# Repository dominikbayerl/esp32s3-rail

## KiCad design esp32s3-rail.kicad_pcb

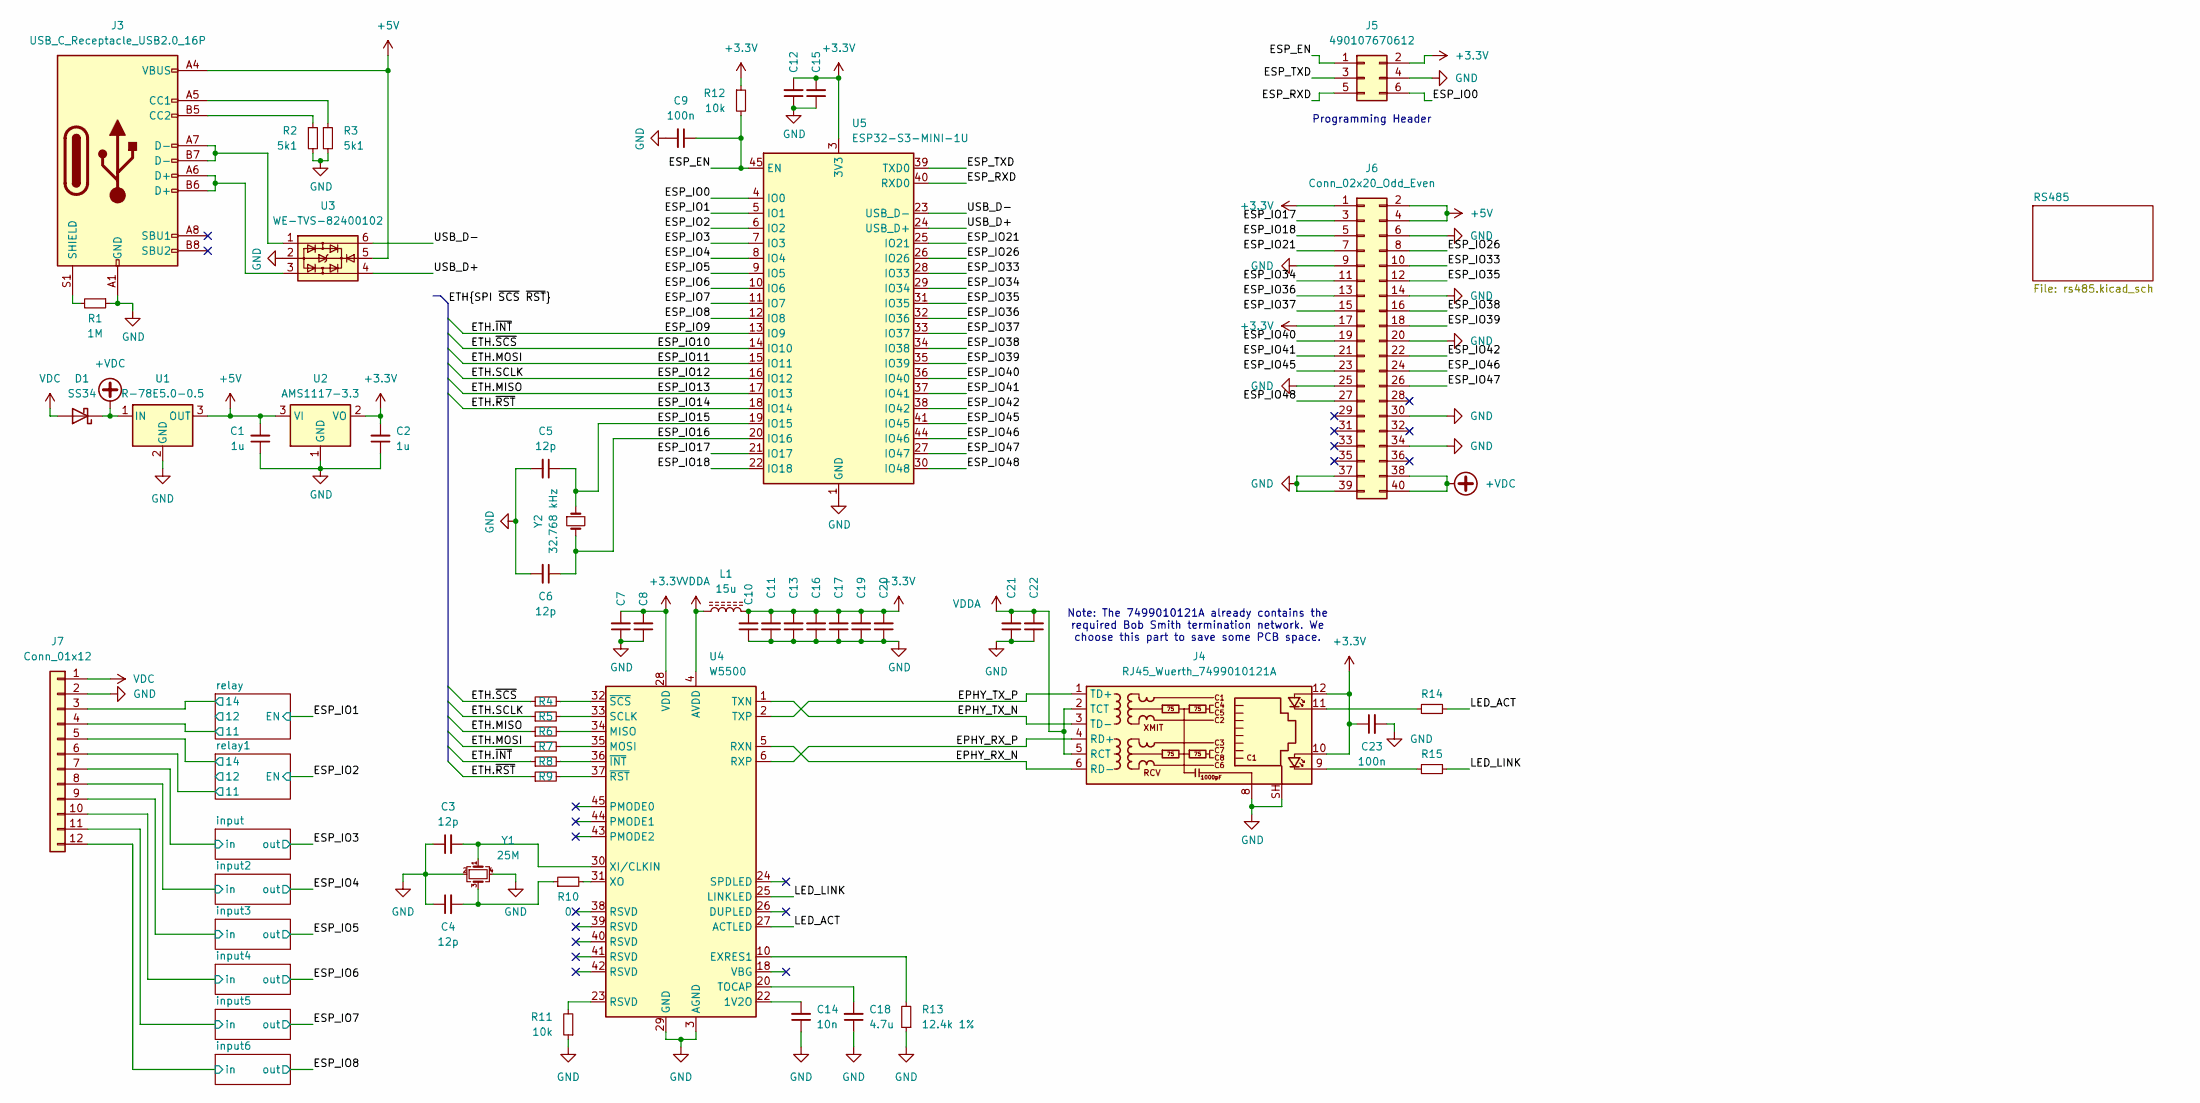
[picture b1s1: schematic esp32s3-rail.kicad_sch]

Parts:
C1, C2, C7, C8, C10, C11, C12, C13, C15, C16, C19, C20: 1u; C_0603_1608Metric_Pad1.08x0.95mm_HandSolder
C3, C4, C5, C6: 12p; C_0603_1608Metric_Pad1.08x0.95mm_HandSolder
C9, C21, C23: 100n; C_0603_1608Metric_Pad1.08x0.95mm_HandSolder
C14: 10n; C_0603_1608Metric_Pad1.08x0.95mm_HandSolder
C17: 10u; C_0603_1608Metric_Pad1.08x0.95mm_HandSolder
C18: 4.7u; C_0603_1608Metric_Pad1.08x0.95mm_HandSolder
C22: 1n; C_0603_1608Metric_Pad1.08x0.95mm_HandSolder
D1: SS34; D_SOD-123
J3: USB_C_Receptacle_USB2.0_16P; USB_C_Receptacle_HRO_TYPE-C-31-M-12
J4: RJ45_Wuerth_7499010121A; RJ45_Wuerth_7499010121A_Horizontal
J5: 490107670612; Würth_WR-WST_debug_490107670612_2x03_P2.54mm_Vertical
J6: Conn_02x20_Odd_Even; PinSocket_2x20_P2.54mm_Vertical
J7: Conn_01x12; Molex_SPOX_5268-12A_1x12_P2.50mm_Horizontal
L1: 15u; L_0603_1608Metric_Pad1.05x0.95mm_HandSolder
R1: 1M; R_0603_1608Metric_Pad0.98x0.95mm_HandSolder
R2, R3: 5k1; R_0603_1608Metric_Pad0.98x0.95mm_HandSolder
R4, R5, R6, R7, R8, R9: 20; R_0603_1608Metric_Pad0.98x0.95mm_HandSolder
R10: 0; R_0603_1608Metric_Pad0.98x0.95mm_HandSolder
R11, R12: 10k; R_0603_1608Metric_Pad0.98x0.95mm_HandSolder
R13: 12.4k 1%; R_0603_1608Metric_Pad0.98x0.95mm_HandSolder
R14, R15: 1k; R_0603_1608Metric_Pad0.98x0.95mm_HandSolder
U1: R-78E5.0-0.5; Converter_DCDC_RECOM_R-78E-0.5_THT
U2: AMS1117-3.3; SOT-223-3_TabPin2
U3: WE-TVS-82400102; SOT-23-6
U4: W5500; LQFP-48_7x7mm_P0.5mm
U5: ESP32-S3-MINI-1U; ESP32-S2-MINI-1U
Y1: 25M; Crystal_SMD_3225-4Pin_3.2x2.5mm_HandSoldering
Y2: 32.768 kHz; Crystal_SMD_3215-2Pin_3.2x1.5mm

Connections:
+3.3V: C2.2, C7.2, C8.2, C10.2, C11.2, C12.2, C13.2, C15.2, C16.2, C17.2, C19.2, C20.2, C23.1, J4.10, J4.12, J5.2, J6.1, J6.17, L1.2, R12.1, U2.2 (VO), U4.28 (VDD), U5.3 (3V3); also elsewhere on the board
+5V: C1.2, J3.A4 (VBUS), J3.A9 (VBUS), J3.B4 (VBUS), J3.B9 (VBUS), J6.2, J6.4, U1.3 (OUT), U2.3 (VI), U3.5; also elsewhere on the board
+VDC: D1.1 (K), J6.38, J6.40, U1.1 (IN)
/EPHY_RX_N: J4.6 (RD-), U4.5 (RXN)
/EPHY_RX_P: J4.4 (RD+), U4.6 (RXP)
/EPHY_TX_N: J4.3 (TD-), U4.1 (TXN)
/EPHY_TX_P: J4.1 (TD+), U4.2 (TXP)
/ESP_EN: C9.1, J5.1, R12.2, U5.45 (EN)
/ESP_IO0: J5.6, U5.4 (IO0)
/ESP_IO1: U5.5 (IO1); also elsewhere on the board
/ESP_IO2: U5.6 (IO2); also elsewhere on the board
/ESP_IO3: U5.7 (IO3); also elsewhere on the board
/ESP_IO4: U5.8 (IO4); also elsewhere on the board
/ESP_IO5: U5.9 (IO5); also elsewhere on the board
/ESP_IO6: U5.10 (IO6); also elsewhere on the board
/ESP_IO7: U5.11 (IO7); also elsewhere on the board
/ESP_IO8: U5.12 (IO8); also elsewhere on the board
/ESP_IO15: C5.1, U5.19 (IO15), Y2.1
/ESP_IO16: C6.1, U5.20 (IO16), Y2.2
/ESP_IO17: J6.3, U5.21 (IO17)
/ESP_IO18: J6.5, U5.22 (IO18)
/ESP_IO21: J6.7, U5.25 (IO21)
/ESP_IO26: J6.8, U5.26 (IO26)
/ESP_IO33: J6.10, U5.28 (IO33)
/ESP_IO34: J6.11, U5.29 (IO34)
/ESP_IO35: J6.12, U5.31 (IO35)
/ESP_IO36: J6.13, U5.32 (IO36)
/ESP_IO37: J6.15, U5.33 (IO37)
/ESP_IO38: J6.16, U5.34 (IO38)
/ESP_IO39: J6.18, U5.35 (IO39)
/ESP_IO40: J6.19, U5.36 (IO40)
/ESP_IO41: J6.21, U5.37 (IO41)
/ESP_IO42: J6.22, U5.38 (IO42)
/ESP_IO45: J6.23, U5.41 (IO45)
/ESP_IO46: J6.24, U5.44 (IO46)
/ESP_IO47: J6.26, U5.27 (IO47)
/ESP_IO48: J6.27, U5.30 (IO48)
/ESP_RXD: J5.5, U5.40 (RXD0)
/ESP_TXD: J5.3, U5.39 (TXD0)
/ETH.MISO: R6.1, U5.17 (IO13)
/ETH.MOSI: R7.1, U5.15 (IO11)
/ETH.SCLK: R5.1, U5.16 (IO12)
/ETH.~INT: R8.1, U5.13 (IO9)
/ETH.~RST: R9.1, U5.18 (IO14)
/ETH.~SCS: R4.1, U5.14 (IO10)
/LED_ACT: R14.2, U4.27 (ACTLED)
/LED_LINK: R15.2, U4.25 (LINKLED)
/USB_D+: U3.4, U5.24 (USB_D+)
/USB_D-: U3.6, U5.23 (USB_D-)
/input2/in: J7.8; also elsewhere on the board
/input3/in: J7.9; also elsewhere on the board
/input4/in: J7.10; also elsewhere on the board
/input5/in: J7.11; also elsewhere on the board
/input6/in: J7.12; also elsewhere on the board
/input/in: J7.7; also elsewhere on the board
/relay1/11: J7.6; also elsewhere on the board
/relay1/14: J7.5; also elsewhere on the board
/relay/11: J7.4; also elsewhere on the board
/relay/14: J7.3; also elsewhere on the board
GND: C1.1, C2.1, C3.1, C4.1, C5.2, C6.2, C7.1, C8.1, C9.2, C10.1, C11.1, C12.1, C13.1, C14.1, C15.1, C16.1, C17.1, C18.1, C19.1, C20.1, C21.1, C22.1, C23.2, J3.A1 (GND), J3.A12 (GND), J3.B1 (GND), J3.B12 (GND), J4.8, J4.SH, J5.4, J6.6, J6.9, J6.14, J6.20, J6.25, J6.30, J6.34, J6.37, J6.39, J7.2, R1.1, R2.2, R3.2, R11.1, R13.1, U1.2 (GND), U2.1 (GND), U3.2, U4.3 (AGND), U4.9 (AGND), U4.14 (AGND), U4.16 (AGND), U4.19 (AGND), U4.29 (GND), U4.48 (AGND), U5.1 (GND), U5.2 (GND), U5.42 (GND), U5.43 (GND), U5.46 (GND), U5.47 (GND), U5.48 (GND), U5.49 (GND), U5.50 (GND), U5.51 (GND), U5.52 (GND), U5.53 (GND), U5.54 (GND), U5.55 (GND), U5.56 (GND), U5.57 (GND), U5.58 (GND), U5.59 (GND), U5.60 (GND), U5.61 (GND), U5.62 (GND), U5.63 (GND), U5.64 (GND), U5.65 (GND), Y1.2, Y1.4; also elsewhere on the board
unnamed: C4.2, R10.1, Y1.3
unnamed: J3.A5 (CC1), R3.1
unnamed: J3.B5 (CC2), R2.1
unnamed: J3.A6 (D+), J3.B6 (D+), U3.3
unnamed: J3.A7 (D-), J3.B7 (D-), U3.1
unnamed: J3.S1 (SHIELD), R1.2
unnamed: J4.9, R15.1
unnamed: J4.11, R14.1
unnamed: R11.2, U4.23 (RSVD)
unnamed: C14.2, U4.22 (1V2O)
unnamed: R13.2, U4.10 (EXRES1)
unnamed: R6.2, U4.34 (MISO)
unnamed: R7.2, U4.35 (MOSI)
unnamed: R5.2, U4.33 (SCLK)
unnamed: C18.2, U4.20 (TOCAP)
unnamed: C3.2, U4.30 (XI/CLKIN), Y1.1
unnamed: R10.2, U4.31 (XO)
unnamed: R8.2, U4.36 (~INT)
unnamed: R9.2, U4.37 (~RST)
unnamed: R4.2, U4.32 (~SCS)
VDC: D1.2 (A), J7.1
VDDA: C21.2, C22.2, J4.2 (TCT), J4.5 (RCT), L1.1, U4.4 (AVDD), U4.8 (AVDD), U4.11 (AVDD), U4.15 (AVDD), U4.17 (AVDD), U4.21 (AVDD)

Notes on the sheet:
Programming Header
Note: The 7499010121A already contains the required Bob Smith termination network. We choose this part to save some PCB space.

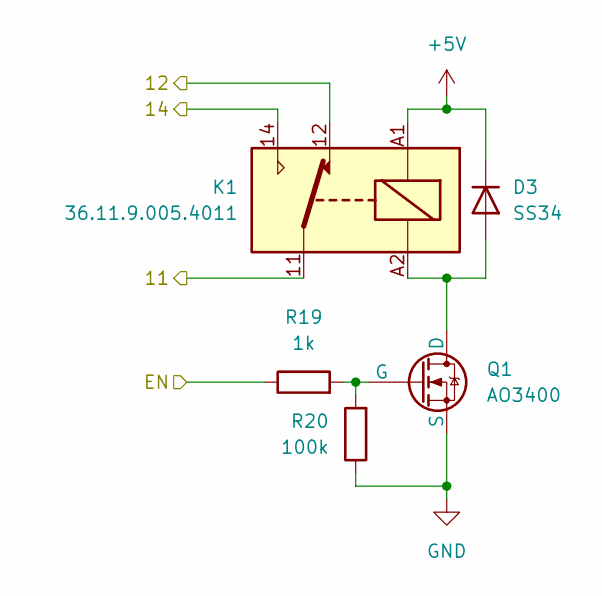
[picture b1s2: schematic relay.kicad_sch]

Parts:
D3: SS34; D_SOD-123
K1: 36.11.9.005.4011; Relay_SPDT_Finder_36.11
Q1: AO3400; SOT-23_Handsoldering
R19: 1k; R_0603_1608Metric_Pad0.98x0.95mm_HandSolder
R20: 100k; R_0603_1608Metric_Pad0.98x0.95mm_HandSolder

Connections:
+5V: D3.1 (K), K1.A1; also elsewhere on the board
/ESP_IO2: R19.1; also elsewhere on the board
/relay1/11: K1.11; also elsewhere on the board
/relay1/12: K1.12
/relay1/14: K1.14; also elsewhere on the board
GND: Q1.3 (S), R20.1; also elsewhere on the board
unnamed: D3.2 (A), K1.A2, Q1.1 (D)
unnamed: Q1.2 (G), R19.2, R20.2

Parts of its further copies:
D6: SS34; D_SOD-123
K2: 36.11.9.005.4011; Relay_SPDT_Finder_36.11
Q2: AO3400; SOT-23_Handsoldering
R27: 1k; R_0603_1608Metric_Pad0.98x0.95mm_HandSolder
R28: 100k; R_0603_1608Metric_Pad0.98x0.95mm_HandSolder

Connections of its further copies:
+5V: D6.1 (K), K2.A1; also elsewhere on the board
/ESP_IO1: R27.1; also elsewhere on the board
/relay/11: K2.11; also elsewhere on the board
/relay/12: K2.12
/relay/14: K2.14; also elsewhere on the board
GND: Q2.3 (S), R28.1; also elsewhere on the board
unnamed: D6.2 (A), K2.A2, Q2.1 (D)
unnamed: Q2.2 (G), R27.2, R28.2

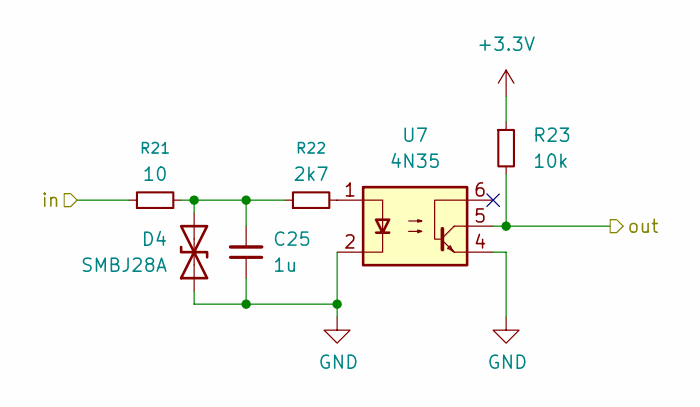
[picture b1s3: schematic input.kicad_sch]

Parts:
C25: 1u; C_0603_1608Metric_Pad1.08x0.95mm_HandSolder
D4: SMBJ28A; D_SMA_Handsoldering
R21: 10; R_0603_1608Metric_Pad0.98x0.95mm_HandSolder
R22: 2k7; R_0603_1608Metric_Pad0.98x0.95mm_HandSolder
R23: 10k; R_0603_1608Metric_Pad0.98x0.95mm_HandSolder
U7: 4N35; DIP-6_W7.62mm

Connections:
+3.3V: R23.1; also elsewhere on the board
/ESP_IO3: R23.2, U7.5; also elsewhere on the board
/input/in: R21.1; also elsewhere on the board
GND: C25.1, D4.1 (A1), U7.2, U7.4; also elsewhere on the board
unnamed: C25.2, D4.2 (A2), R21.2, R22.1
unnamed: R22.2, U7.1

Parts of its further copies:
C26, C27, C28, C29, C30: 1u; C_0603_1608Metric_Pad1.08x0.95mm_HandSolder
D5, D7, D8, D9, D10: SMBJ28A; D_SMA_Handsoldering
R24, R29, R32, R35, R38: 10; R_0603_1608Metric_Pad0.98x0.95mm_HandSolder
R25, R30, R33, R36, R39: 2k7; R_0603_1608Metric_Pad0.98x0.95mm_HandSolder
R26, R31, R34, R37, R40: 10k; R_0603_1608Metric_Pad0.98x0.95mm_HandSolder
U8, U9, U10, U11, U12: 4N35; DIP-6_W7.62mm

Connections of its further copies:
+3.3V: R26.1, R31.1, R34.1, R37.1, R40.1; also elsewhere on the board
/ESP_IO4: R31.2, U9.5; also elsewhere on the board
/ESP_IO5: R26.2, U8.5; also elsewhere on the board
/ESP_IO6: R34.2, U10.5; also elsewhere on the board
/ESP_IO7: R37.2, U11.5; also elsewhere on the board
/ESP_IO8: R40.2, U12.5; also elsewhere on the board
/input2/in: R29.1; also elsewhere on the board
/input3/in: R24.1; also elsewhere on the board
/input4/in: R32.1; also elsewhere on the board
/input5/in: R35.1; also elsewhere on the board
/input6/in: R38.1; also elsewhere on the board
GND: C26.1, C27.1, C28.1, C29.1, C30.1, D5.1 (A1), D7.1 (A1), D8.1 (A1), D9.1 (A1), D10.1 (A1), U8.2, U8.4, U9.2, U9.4, U10.2, U10.4, U11.2, U11.4, U12.2, U12.4; also elsewhere on the board
unnamed: C26.2, D5.2 (A2), R24.2, R25.1
unnamed: C27.2, D7.2 (A2), R29.2, R30.1
unnamed: C28.2, D8.2 (A2), R32.2, R33.1
unnamed: C29.2, D9.2 (A2), R35.2, R36.1
unnamed: C30.2, D10.2 (A2), R38.2, R39.1
unnamed: R25.2, U8.1
unnamed: R30.2, U9.1
unnamed: R33.2, U10.1
unnamed: R36.2, U11.1
unnamed: R39.2, U12.1

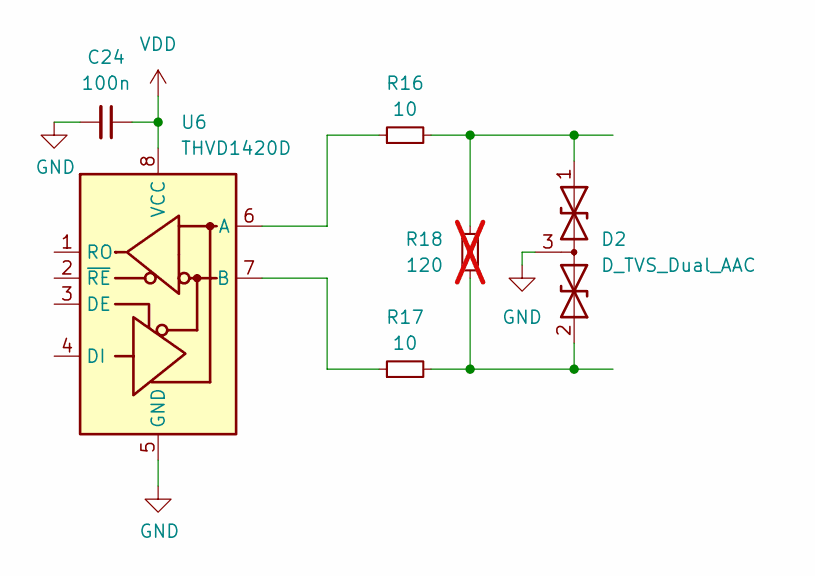
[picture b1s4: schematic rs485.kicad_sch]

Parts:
C24: 100n
D2: D_TVS_Dual_AAC; SOT-23
R16, R17: 10; R_1206_3216Metric
R18: 120; R_1206_3216Metric; not fitted
U6: THVD1420D; SOIC-8_3.9x4.9mm_P1.27mm

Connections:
unnamed: C24.1, U6.8 (VCC)
unnamed: C24.2, D2.3 (common), U6.5 (GND)
unnamed: D2.1 (A1), R16.2, R18.2
unnamed: D2.2 (A2), R17.2, R18.1
unnamed: R16.1, U6.6 (A)
unnamed: R17.1, U6.7 (B)

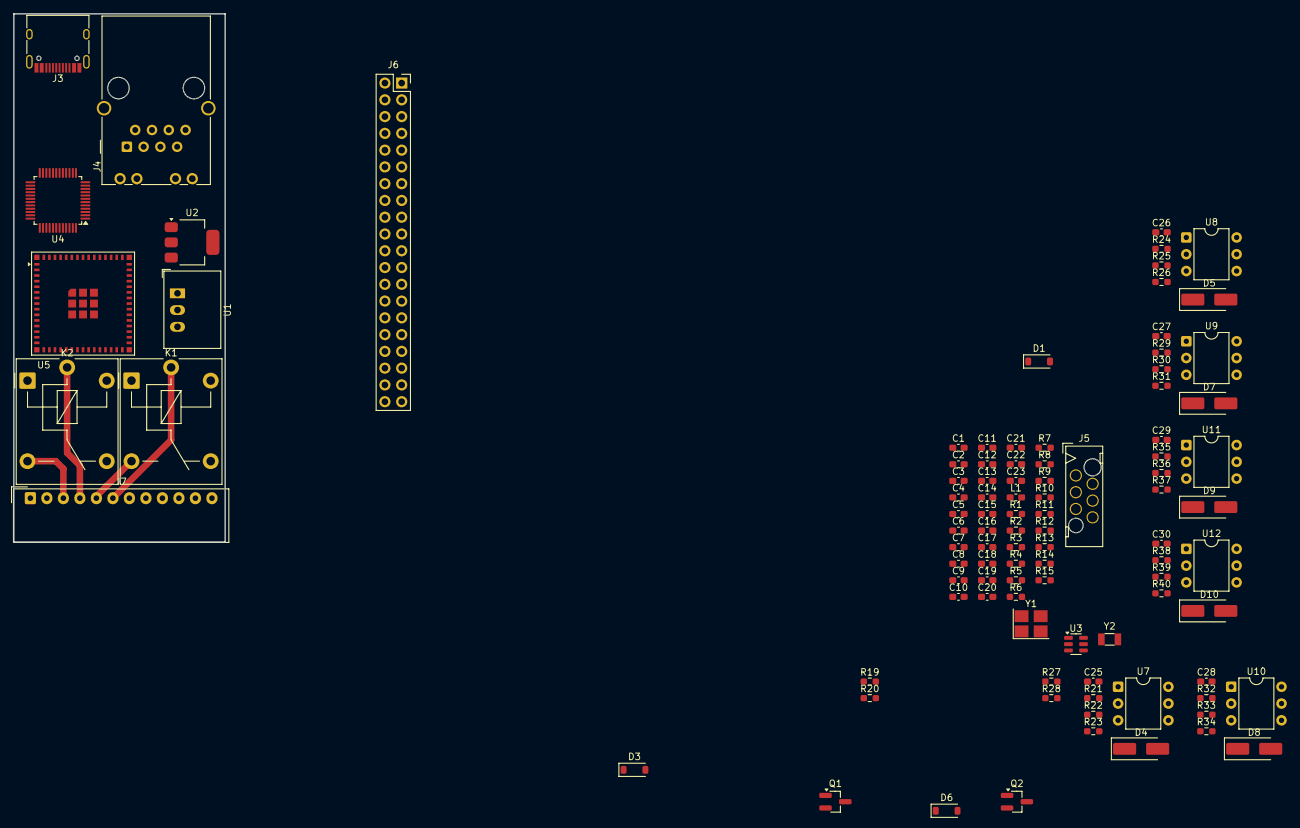
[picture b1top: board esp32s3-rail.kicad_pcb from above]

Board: 2 copper layers, 32.0 x 80.0 mm, 98 parts (0 on the bottom side), 98 nets.

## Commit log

2025-04-17 Initial import.
2025-04-17 Add Wuerth WR-WST connector footprints.
2025-04-25 Update schematic: - Add RS485 ports - Add USB ports - Add 24V I/O ports
2025-05-07 Finish rev0 schematics.
2025-05-07 Assign footprints.
2025-05-09 Update stacking header.
